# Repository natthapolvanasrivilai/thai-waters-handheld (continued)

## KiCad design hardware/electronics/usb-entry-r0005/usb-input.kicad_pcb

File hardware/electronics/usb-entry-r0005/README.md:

# R0005 fast-path experiment — rejected

R0005 establishes a real V2-only power disconnect at A1 LRC4 and distinguishes the protected J8-1 tail from the raw J5 receptacle. All seventeen R0004 A5 footprint placements remain fixed. A new ferrite, VBUS TVS and separate lamp wire land fit on the original 23 × 16 mm board. The [component schedule](bom.csv), [schematic](circuit.pdf), [native layout](usb-input.kicad_pcb), [supplier-net check](boundary.json) and [assembly contacts](assembly.csv) describe this experiment.

**Use the [R0006 passive-limit design](../usb-entry-r0006/README.md) for the current engineering candidate.** R0005's TPS2553 path depends on two external control inputs. Neither input has an implemented source in a standalone R0005 handheld. Floating both inputs safely disables PMIC power and charging.

The 42 R0005 decks took 78 measurements. They yielded 56 within limits, nine characterization readings, nine expected fault failures and four failures of intended operating limits. The identical stock bypass gives 348.837 mA. The intercepted 15 Ω fixture gives 75.769 mA with the weak path enabled. A shorted lamp and PMIC give 96.260 mA in weak mode, 344.499 mA on the configured switch and 436.937 mA with both paths enabled. The 3.60 kΩ lamp resistor reduces the pressed-to-ground lamp fault in suspend to 2.223 mA including the aggregate raw-control allowance. Reinstalling the 2.70 kΩ resistor gives 2.714 mA. The 0.3 µH cable and ideal host with a 2 µs or 10 µs delay before the short-current clamp produce 5.465 A and 12.287 A source peaks. These are source-dependent behavioral stresses. With no battery, the 330 mA-at-3.9 V load yields only 0.805 V pregrant and 3.098 V in low-ILIM configured mode. [Simulation summary](verification.json) · [All readings](measurements.csv) · [Decks and logs](decks-and-logs.zip) · [TI response-time data](https://www.ti.com/lit/ds/symlink/tps2553-q1.pdf)

Reproduce with `python replay.py --engine PATH/TO/ngspice`. The R0006 replay imports the case runner from this file. The original R0012 branch, results and fault injection remain in [the prior review](../../verification/r0012/README.md).

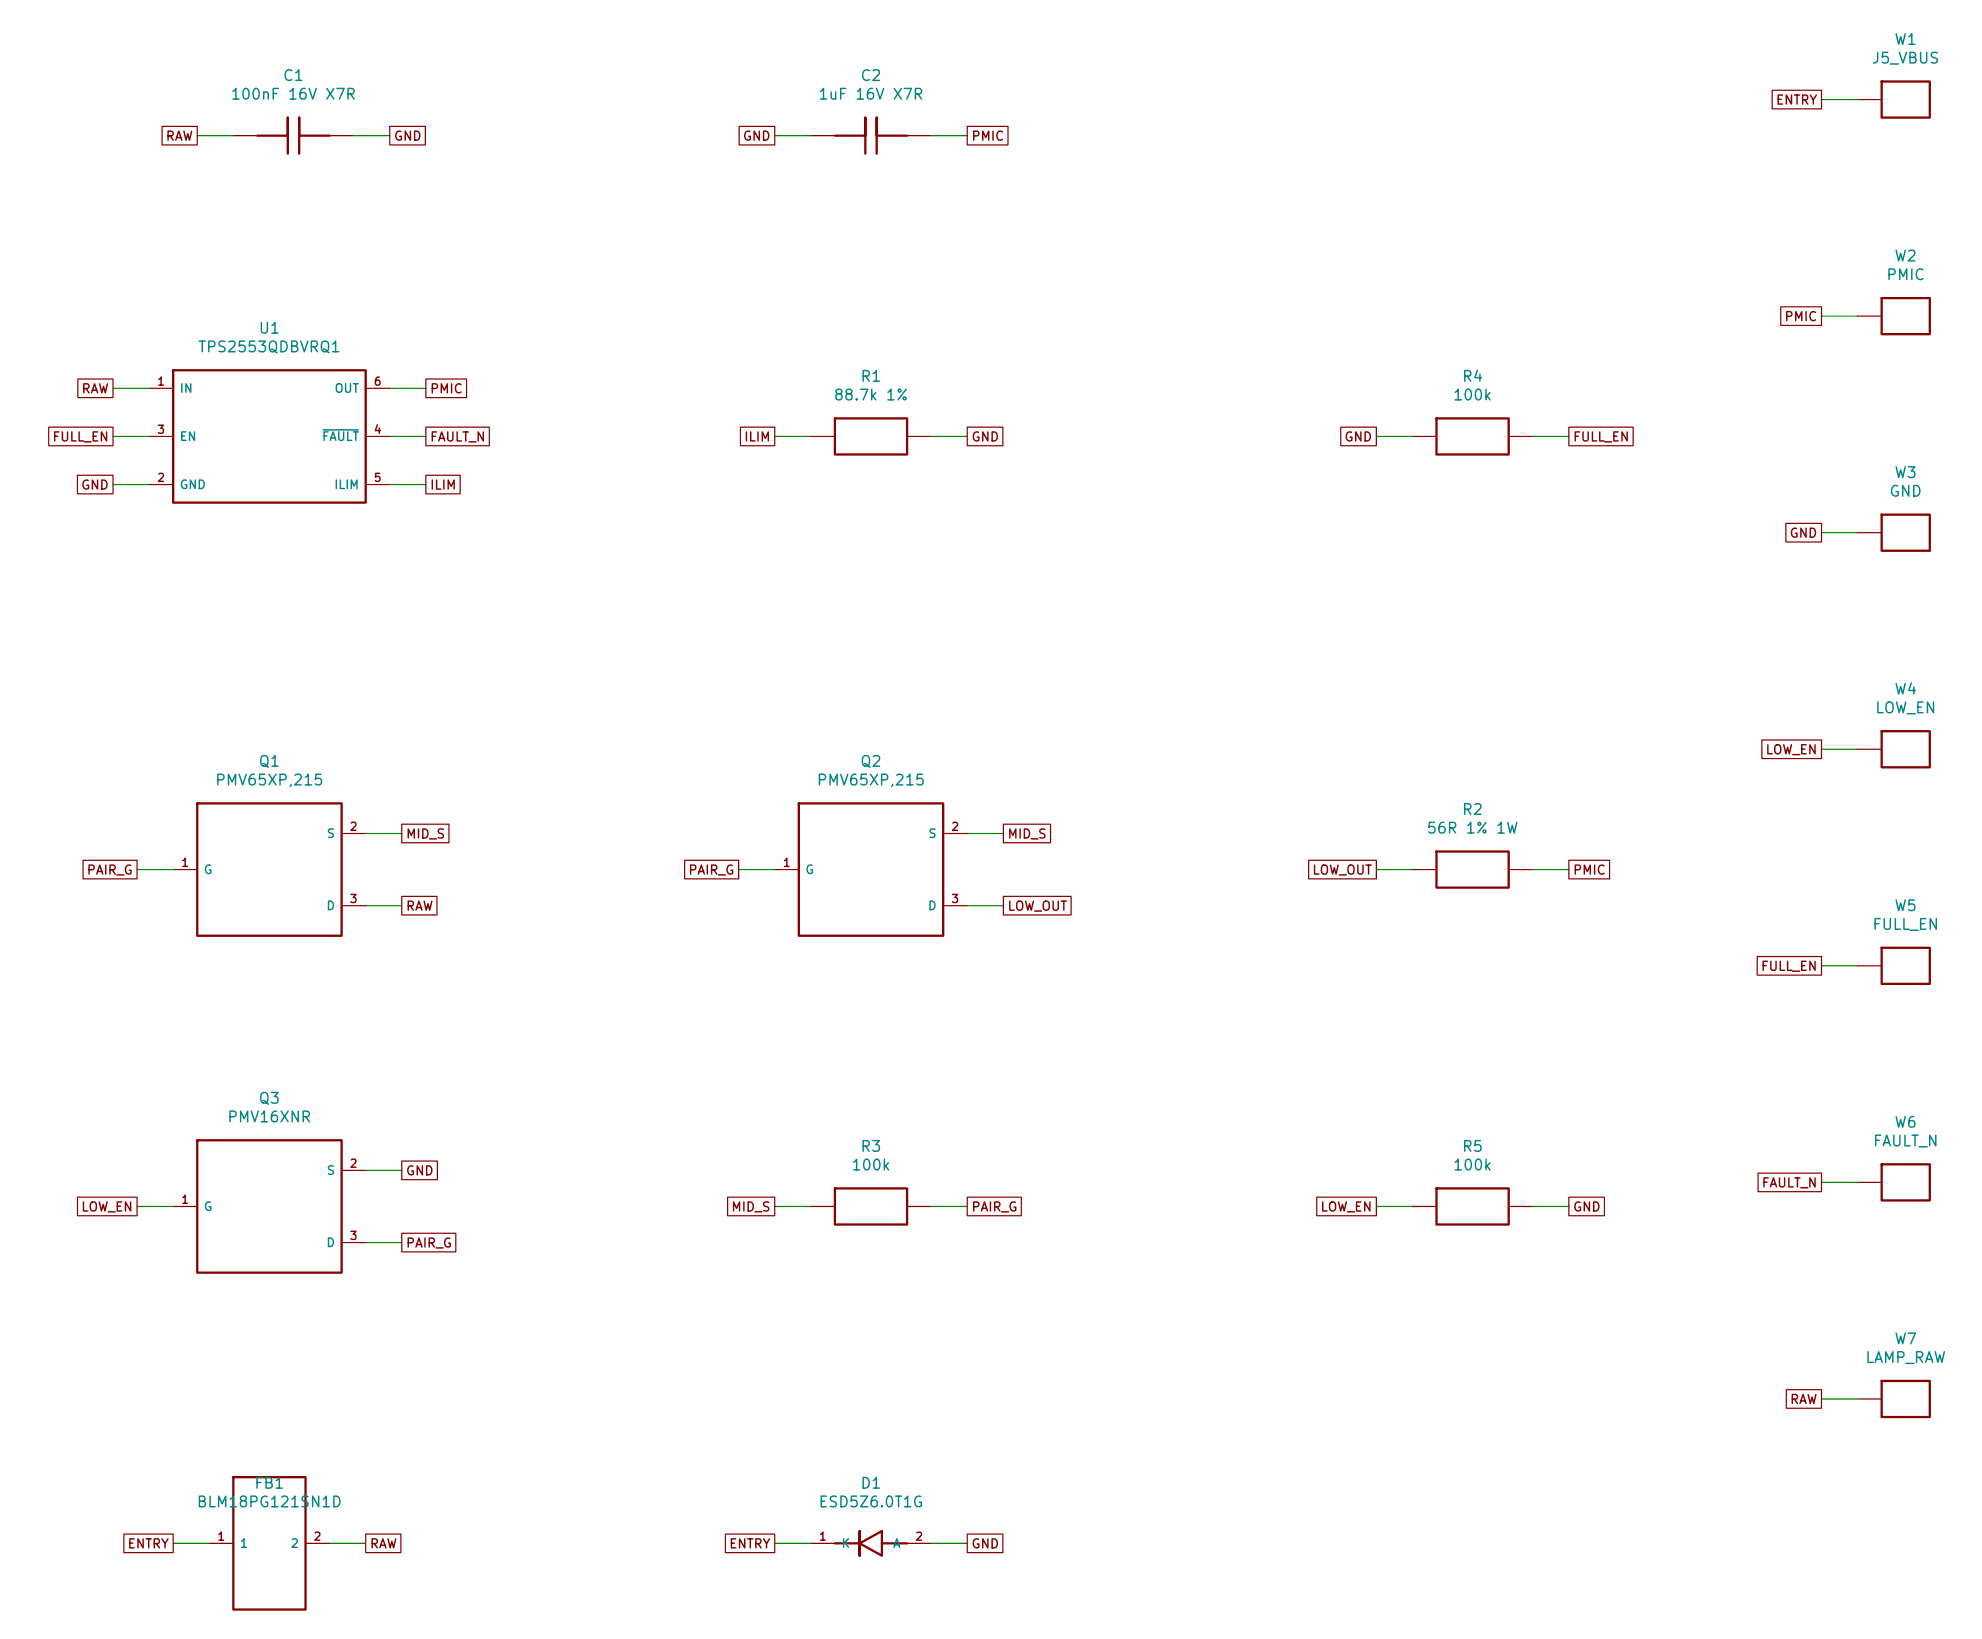
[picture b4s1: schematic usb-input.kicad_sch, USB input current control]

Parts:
C1: 100nF 16V X7R; C_0603_1608Metric
C2: 1uF 16V X7R; C_0603_1608Metric
D1: ESD5Z6.0T1G; D_SOD-523
FB1: BLM18PG121SN1D; L_0603_1608Metric
Q1, Q2: PMV65XP,215; SOT-23
Q3: PMV16XNR; SOT-23
R1: 88.7k 1%; R_0603_1608Metric
R2: 56R 1% 1W; R_2512_6332Metric
R3, R4, R5: 100k; R_0603_1608Metric
U1: TPS2553QDBVRQ1; SOT-23-6
W1: J5_VBUS; SolderWire-0.127sqmm_1x01_D0.48mm_OD1mm
W2: PMIC; SolderWire-0.127sqmm_1x01_D0.48mm_OD1mm
W3: GND; SolderWire-0.127sqmm_1x01_D0.48mm_OD1mm
W4: LOW_EN; SolderWire-0.127sqmm_1x01_D0.48mm_OD1mm
W5: FULL_EN; SolderWire-0.127sqmm_1x01_D0.48mm_OD1mm
W6: FAULT_N; SolderWire-0.127sqmm_1x01_D0.48mm_OD1mm
W7: LAMP_RAW; SolderWire-0.127sqmm_1x01_D0.48mm_OD1mm

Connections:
ENTRY: D1.1 (K), FB1.1, W1.1
FAULT_N: U1.4 (~FAULT), W6.1
FULL_EN: R4.2, U1.3 (EN), W5.1
GND: C1.2, C2.1, D1.2 (A), Q3.2 (S), R1.2, R4.1, R5.2, U1.2 (GND), W3.1
ILIM: R1.1, U1.5 (ILIM)
LOW_EN: Q3.1 (G), R5.1, W4.1
LOW_OUT: Q2.3 (D), R2.1
MID_S: Q1.2 (S), Q2.2 (S), R3.1
PAIR_G: Q1.1 (G), Q2.1 (G), Q3.3 (D), R3.2
PMIC: C2.2, R2.2, U1.6 (OUT), W2.1
RAW: C1.1, FB1.2, Q1.3 (D), U1.1 (IN), W7.1

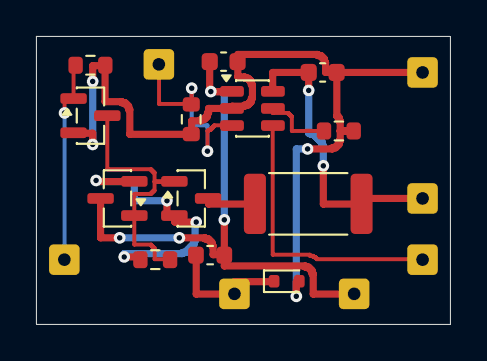
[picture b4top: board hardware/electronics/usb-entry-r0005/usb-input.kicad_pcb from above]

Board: 2 copper layers, 23.0 x 16.0 mm, 20 parts (0 on the bottom side), 11 nets.
